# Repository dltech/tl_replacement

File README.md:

A replacement for a driver in old ATX power suplies. May be conected direcly to
the coils of isolaton transformer. Powered by Vsb and controls only one channel
by current and volage. Includes submodule with display and simple menu. 
Functions:

Short circuit protection (checks every 0.1ms).

Current and voltage stabilization.

Mode for control charging 12V and 6V lead acid batteries.

Fan speed control.

It is based on libopencm3 libraries
# Instructions
 1. git clone https://github.com/libopencm3/libopencm3-template.git zarjadnik
 2. cd zarjadnik
 3. git submodule update --init # (Only needed once)
 4. make -C libopencm3 # (Only needed once)
 5. make -C zarjadnik

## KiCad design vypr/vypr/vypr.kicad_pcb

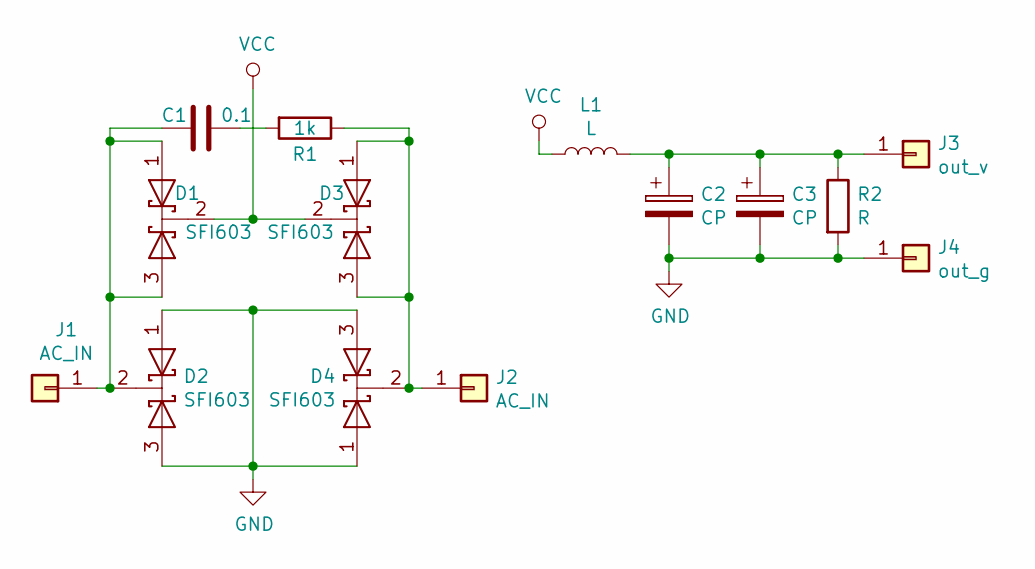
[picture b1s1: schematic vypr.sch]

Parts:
C1: 0.1; C_Disc_D6.0mm_W2.5mm_P5.00mm
C2, C3: CP; CP_Radial_D17.0mm_P7.50mm
D1, D2, D3, D4: SFI603; TO-220-3_Vertical
J1, J2: AC_IN; SolderWirePad_1x01_SMD_5x10mm
J3: out_v; SolderWirePad_1x01_SMD_5x10mm
J4: out_g; SolderWirePad_1x01_SMD_5x10mm
L1: L; L_Toroid_Vertical_L35.6mm_W17.8mm_P12.70mm_Pulse_E
R1: 1k; R_Axial_DIN0207_L6.3mm_D2.5mm_P7.62mm_Horizontal
R2: R; R_Axial_DIN0516_L15.5mm_D5.0mm_P7.62mm_Vertical

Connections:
GND: C2.2, C3.2, D2.1 (A), D2.3 (A), D4.1 (A), D4.3 (A), J4.1, R2.2
unnamed: C1.1, D1.1 (A), D1.3 (A), D2.2 (K), J1.1
unnamed: C1.2, R1.2
unnamed: C2.1, C3.1, J3.1, L1.2, R2.1
unnamed: D3.1 (A), D3.3 (A), D4.2 (K), J2.1, R1.1
VCC: D1.2 (K), D3.2 (K), L1.1

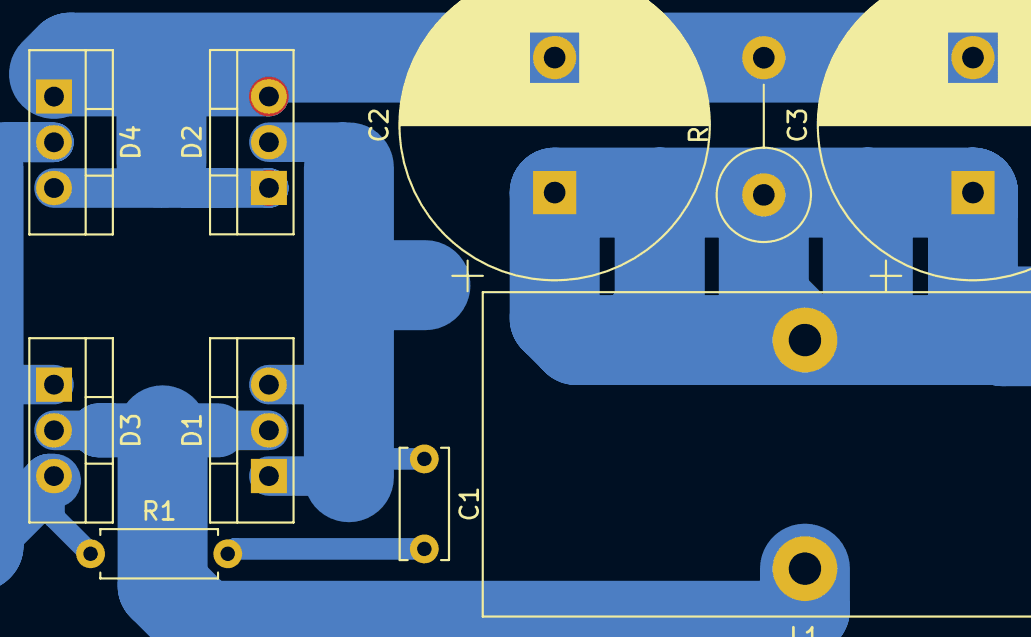
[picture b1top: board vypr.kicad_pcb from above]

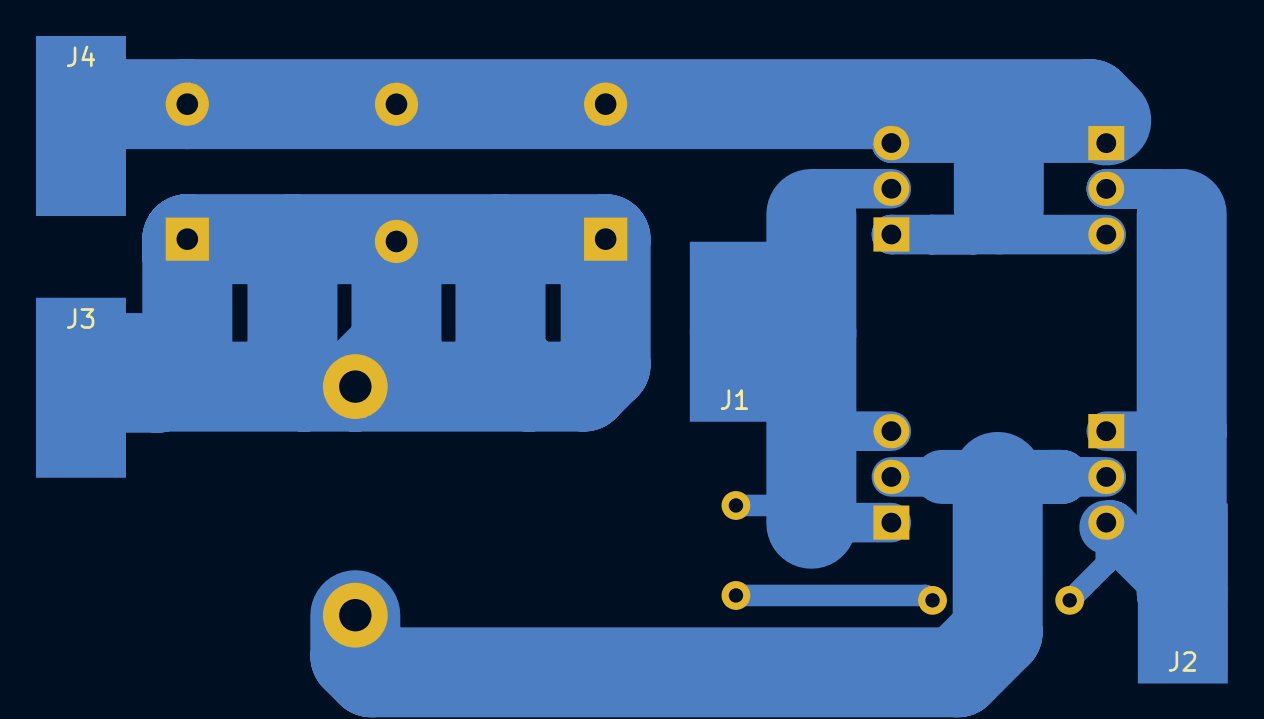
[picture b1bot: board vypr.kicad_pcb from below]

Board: 2 copper layers, 14 parts (4 on the bottom side), 6 nets.

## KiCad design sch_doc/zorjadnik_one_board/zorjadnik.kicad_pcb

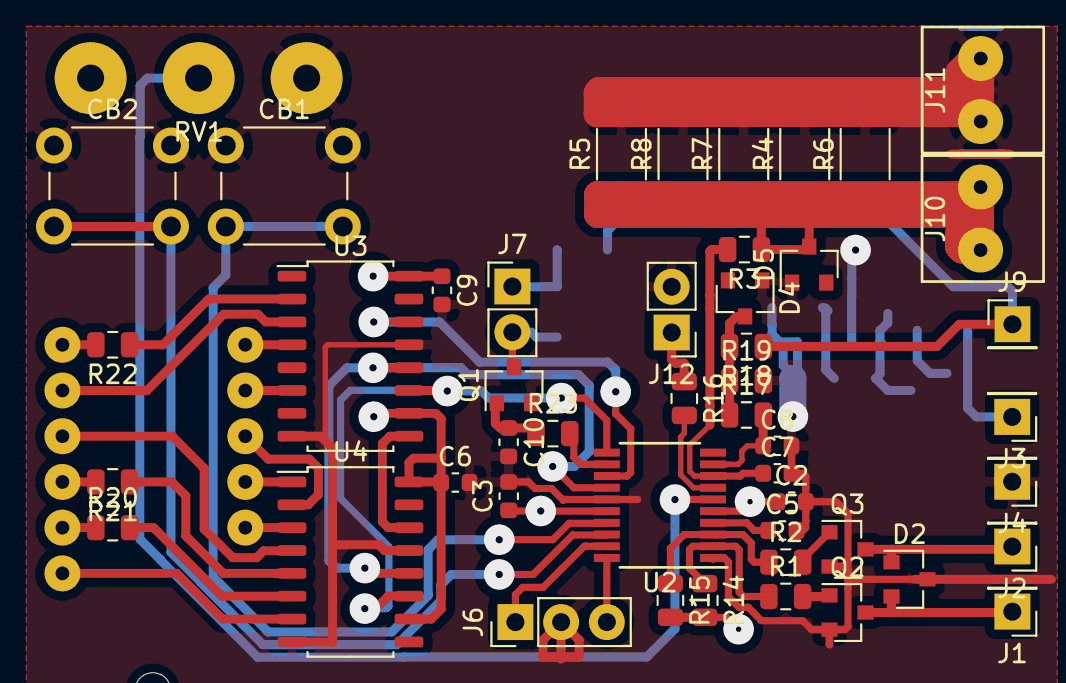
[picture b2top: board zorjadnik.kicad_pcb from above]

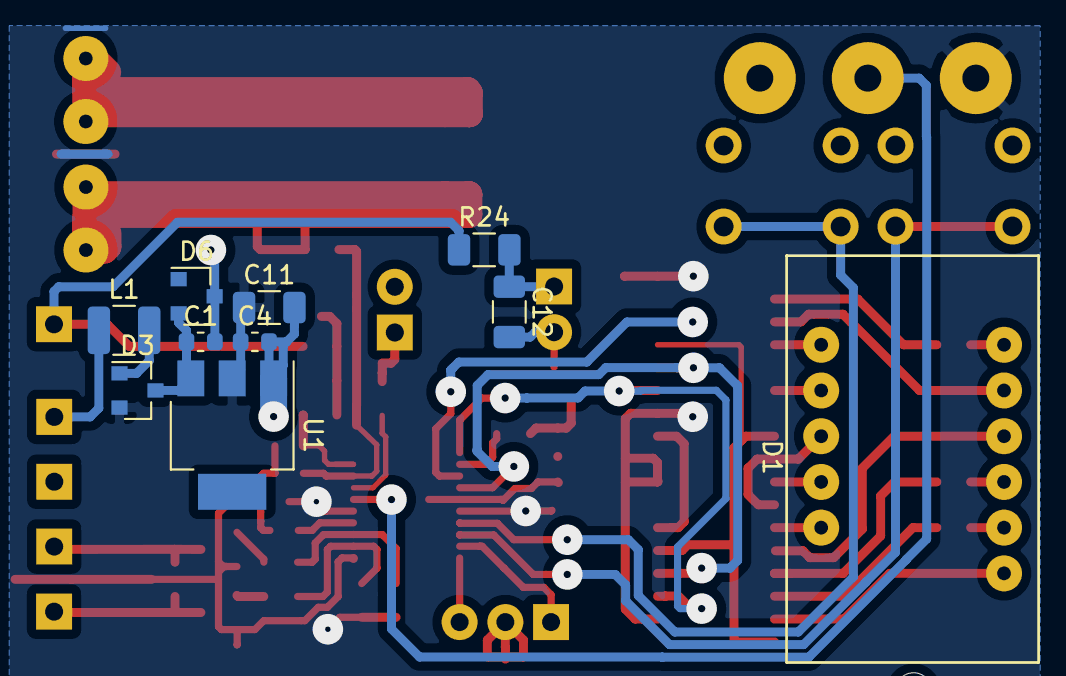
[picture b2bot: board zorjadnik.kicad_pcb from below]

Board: 2 copper layers, 58 parts (10 on the bottom side), 44 nets.

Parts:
C1, C2, C5, C10: 0.1; C_0603_1608Metric
C3, C4, C6, C9: 100nF; C_0603_1608Metric
C7, C8: 10n; C_0603_1608Metric
C11, C12: 10µF; C_1206_3216Metric
CB1: mode; SW_PUSH_6mm
CB2: select; SW_PUSH_6mm
D1: LED_3digit; FYT-3631_minimal
D2: BAT54; SOT-23
D3: BAV70; SOT-23
D4, D5: D_Zener; SOT-23
D6: PESD1CAN; D_SOT-23_NKA
J1: OUT1; PinHeader_1x01_P2.54mm_Vertical
J2: OUT2; PinHeader_1x01_P2.54mm_Vertical
J3: Vsb; PinHeader_1x01_P2.54mm_Vertical
J4: GND; PinHeader_1x01_P2.54mm_Vertical
J6: firmware; PinHeader_1x03_P2.54mm_Vertical
J7: cooling fan; PinHeader_1x02_P2.54mm_Vertical
J9: power supply Vout; PinHeader_1x01_P2.54mm_Vertical
J10: output GND; KF350x2
J11: power supply GND; KF350x2
J12: spare port; PinHeader_1x02_P2.54mm_Vertical
L1: 47µH; L_1210_3225Metric
Q1: BCR512; SOT-23
Q2, Q3: BCR108; SOT-23
R1, R2, R23: 100; R_0805_2012Metric
R3, R14, R15, R17: 1k; R_0805_2012Metric
R4, R5, R6, R7, R8: 0.1R; R_2010_5025Metric
R16: 1.5k; R_0805_2012Metric
R18: 4.7k; R_0805_2012Metric
R19: 510; R_0805_2012Metric
R20, R21, R22: 200; R_0805_2012Metric
R24: 63; R_1206_3216Metric
RV1: POT; СП3-4
U1: AP1117-33; SOT-223
U2: STM32F030F4Px; TSSOP-20_4.4x6.5mm_P0.65mm
U3, U4: 74HC595; SOP-16_4.55x10.3mm_P1.27mm

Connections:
+3V3: C2.1, C3.1, C4.1, C6.1, C9.1, C11.1, D3.2, R14.2, R15.2, RV1.3, U1.2, U2.5, U2.16, U3.10, U3.16, U4.10, U4.16
+28V: J3.1, L1.1
+VDC: J9.1, R18.1, R24.1
/SWCLK: J6.3, U2.20
/SWDIO: J6.1, U2.19
/Sheet5D41F71D/A: D1.11, U3.3
/Sheet5D41F71D/B: D1.7, U4.7
/Sheet5D41F71D/C: D1.4, U4.1
/Sheet5D41F71D/D: D1.2, U3.6
/Sheet5D41F71D/D1: R22.1, U3.2
/Sheet5D41F71D/D2: R21.1, U4.5
/Sheet5D41F71D/D3: R20.2, U4.6
/Sheet5D41F71D/DP: D1.3, U4.2
/Sheet5D41F71D/E: D1.1, U3.4
/Sheet5D41F71D/F: D1.10, U4.4
/Sheet5D41F71D/G: D1.5, U4.3
GND: C1.2, C2.2, C3.2, C4.2, C5.2, C6.2, C7.2, C8.2, C9.2, C10.2, C11.2, CB1.1, CB2.1, D2.3, D4.1, D5.1, D6.2, J4.1, J6.2, J11.1, J11.2, J12.2, Q1.2, Q2.2, Q3.2, R4.2, R5.2, R6.2, R7.2, R8.2, R19.2, RV1.1, U1.1, U2.1, U2.15, U3.8, U3.13, U4.8, U4.13
MOSI: U2.13, U3.14
unnamed: C1.1, D3.3, D6.1, U1.3
unnamed: C5.1, U2.4
unnamed: C7.1, R3.2, U2.8
unnamed: C8.1, R17.2, U2.9
unnamed: C10.1, Q1.1, R23.1
unnamed: C12.1, J7.1, R24.2
unnamed: C12.2, J7.2, Q1.3
unnamed: D1.8, R20.1
unnamed: D1.9, R21.2
unnamed: D1.12, R22.2
unnamed: D2.1, J2.1, Q3.3
unnamed: D2.2, J1.1, Q2.3
unnamed: D3.1, L1.2
unnamed: D4.3, R17.1, R18.2, R19.1
unnamed: D5.3, J10.1, J10.2, R3.1, R4.1, R5.1, R6.1, R7.1, R8.1
unnamed: J12.1, R16.1
unnamed: R1.1, R14.1, U2.2
unnamed: R2.1, R15.1, U2.3
unnamed: R16.2, U2.7
unnamed: R23.2, U2.12
unnamed: U3.9, U4.14
SCK: U2.11, U3.11, U4.11
ST_CP: U2.14, U3.12, U4.12
mode_but: CB1.2, U2.17
pot: RV1.2, U2.6
sel_but: CB2.2, U2.18

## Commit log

2019-11-05 протестированный вариант зарядника с защитой по питанию драйвера
2019-11-09 навел красивостей в схеме
2019-11-09 навел порядок в datasheets
2019-11-26 что то подкрутил
2020-01-13 поаккуратней схема
2020-01-23 немного комментариев в коде, вариант с одной платой (одна 5х3 вместо двух 3х3)
2020-01-29 собрал
2020-02-13 полирнул меню, теперь есть функция выкючения
2020-02-16 список компонентов
2020-02-21 еще покрутил меню
2020-02-23 убрал сохранение настроек, не умею в такое
2020-02-27 добавил сохрааниение настроек, подправил переменник, не проверял
2020-03-07 раньше повисал теперь не висит
2020-04-06 переменник постабильней
2020-06-19 наладил, как сделаю трансформатор, так будет релиз
2021-08-28 new sch
2022-04-29 new parts pdf's
